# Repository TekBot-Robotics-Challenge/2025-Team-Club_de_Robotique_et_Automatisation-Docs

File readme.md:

Ceci est un dossier pour rassembler des archives photos du groupe.

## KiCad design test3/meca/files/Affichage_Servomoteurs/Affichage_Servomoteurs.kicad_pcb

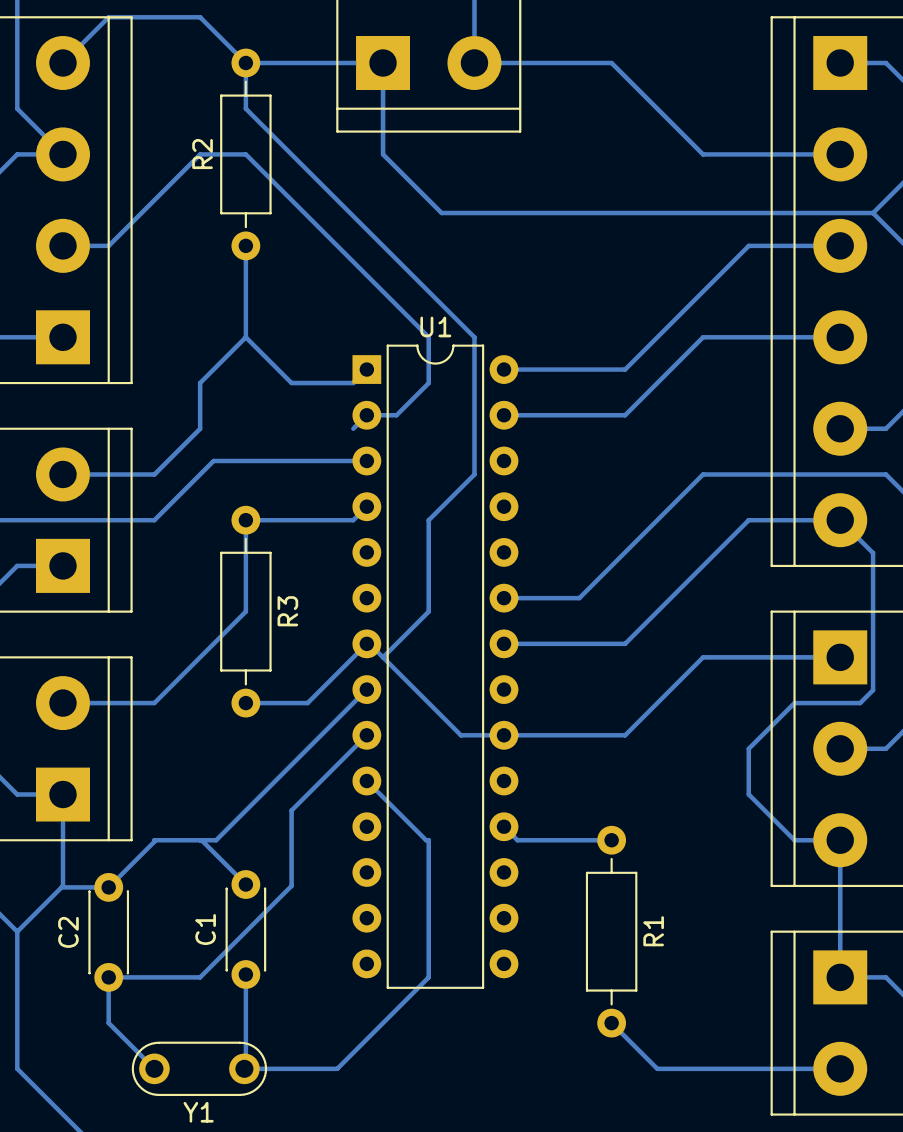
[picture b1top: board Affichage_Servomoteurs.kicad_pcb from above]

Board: 2 copper layers, 14 parts (0 on the bottom side), 13 nets.

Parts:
BP1: RESET; TerminalBlock_bornier-2_P5.08mm
BP2: ARRET; TerminalBlock_bornier-2_P5.08mm
C1, C2: 22pF; C_Disc_D4.3mm_W1.9mm_P5.00mm
D1: LED; TerminalBlock_bornier-2_P5.08mm
J1: PCA9685; TerminalBlock_bornier-6_P5.08mm
J2: FTDI; TerminalBlock_bornier-4_P5.08mm
J3: +5V; TerminalBlock_bornier-2_P5.08mm
R1: 220; R_Axial_DIN0207_L6.3mm_D2.5mm_P10.16mm_Horizontal
R2, R3: 1K; R_Axial_DIN0207_L6.3mm_D2.5mm_P10.16mm_Horizontal
RV1: 10K; TerminalBlock_bornier-3_P5.08mm
U1: ATmega328-P; DIP-28_W7.62mm
Y1: Quartz; Resonator-2Pin_W7.0mm_H2.5mm

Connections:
A0: RV1.2, U1.23 (PC0)
unnamed: D1.2 (A), R1.2
unnamed: R1.1, U1.18 (PB4)
unnamed: BP2.2 (A), R3.1, U1.4 (PD2)
unnamed: C2.1, U1.9 (XTAL1/PB6), Y1.2
unnamed: C1.1, U1.10 (XTAL2/PB7), Y1.1
unnamed: BP1.2 (A), R2.1, U1.1 (~RESET/PC6)
OE: BP1.1 (A), BP2.1 (A), C1.2, C2.2, D1.1 (K), J1.2, J1.6, J2.3, J3.2, RV1.3, U1.8 (GND), U1.22 (GND)
RXD: J2.2, U1.2 (PD0)
SCL: J1.3, U1.28 (PC5)
SDA: J1.4, U1.27 (PC4)
TXD: J2.1, U1.3 (PD1)
V+: J1.1, J1.5, J2.4, J3.1, R2.2, R3.2, RV1.1, U1.7 (VCC), U1.20 (AVCC)

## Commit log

2025-06-12 Create Test1_IT
2025-06-12 Create Test 1 Mécanique
2025-06-12 Create Introduction Générale
2025-06-12 Create images
2025-06-12 Create Video
2025-06-13 Rename readme.md to Explication.md
2025-06-13 Rename Doc.md to Doc.md
2025-06-13 Rename TEST 1 ELECTRONIQUE /French/images/1.png to TEST 1 ELECTRONIQUE /images /1.png
2025-06-13 Rename TEST 1 ELECTRONIQUE /French/images/2.png to TEST 1 ELECTRONIQUE /images /2.png
2025-06-13 Rename TEST 1 ELECTRONIQUE /French/images/3.png to TEST 1 ELECTRONIQUE /images/3.png
2025-06-13 Rename TEST 1 ELECTRONIQUE /French/images/4.png to TEST 1 ELECTRONIQUE /images/4.png
2025-06-13 Rename TEST 1 ELECTRONIQUE /French/images/5.png to TEST 1 ELECTRONIQUE /images /5.png
2025-06-13 Rename TEST 1 ELECTRONIQUE /French/images/6.png to TEST 1 ELECTRONIQUE /images/6.png
2025-06-13 Rename TEST 1 ELECTRONIQUE /French/images/7.jpg to TEST 1 ELECTRONIQUE /images/7.jpg
2025-06-13 Rename TEST 1 ELECTRONIQUE /French/images/8.jpg to TEST 1 ELECTRONIQUE /images /8.jpg
2025-06-13 Rename TEST 1 ELECTRONIQUE /French/images/9.png to TEST 1 ELECTRONIQUE /images/9.png
2025-06-13 Rename TEST 1 ELECTRONIQUE /French/images/readme.md to TEST 1 ELECTRONIQUE /images/readme.md
2025-06-13 Rename 1.png to 1.png
2025-06-13 Rename 5.png to 5.png
2025-06-13 Rename 8.jpg to 8.jpg
2025-06-13 Rename DOCUMENTATION TECHNIQUE DES TESTS EN ELECTRONIQUE.pdf to DOCUMENTATION TECHNIQUE DES TESTS EN ELECTRONIQUE.pdf
2025-06-13 Rename Explication.md to Explication.md
2025-06-13 Rename Test1.ino to Test1.ino
2025-06-13 Rename TEST 1 ELECTRONIQUE /French_Doc /Explication.md to TEST 1 ELECTRONIQUE /French_Doc /Partie_Code/Explication.md
2025-06-13 Rename TEST 1 ELECTRONIQUE /Partie Code/Test1.ino to TEST 1 ELECTRONIQUE /French_Doc /Partie Code/Test1.ino
2025-06-14 Rename Conclusin_Général.md to Conclusion_Général.md
2025-06-14 Dépot archives
2025-06-14 Ajout du dossier Archives
2025-06-14 Ajout de nouveaux dossiers et fichiers
2025-06-14 Suppression du dossier Archives
2025-06-14 Ajout des modifications et nouveaux fichiers
2025-06-14 Ajout de tous les fichiers présents dans le dépôt local
2025-06-14 Déplacement du dossier images vers DOCUMENTATION
2025-06-14 Rename TESTS 1/POLE ELECTRONIQUE/images/1.png to TESTS 1/POLE ELECTRONIQUE/English_Doc/DOCUMENTATION/images/1.png
2025-06-15 Mises à jour locales après synchronisation
2025-06-19 Ajout de la page de la doc meca Test1
2025-06-19 Ajout de notre page
2025-06-20 Ajout de notre page modifiée
2025-06-21 Ajout de notre page modifiée !
2025-06-21 Auto Deploy CI/CD
2025-07-26 Test final
2025-07-26 Ajout
2025-07-26 Modification
